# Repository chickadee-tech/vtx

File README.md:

# Chickadee Tech MicroSD Polystack Mod #
This mod adds a VTX to a Polystack.

## Documentation ##
See the [wiki](https://github.com/chickadee-tech/vtx/wiki) for documentation.

## Polystack ##
This **mod** board is part of the Polystack platform for modular microcontrol systems. More information on the platform can be found at [polystack.org](http://polystack.org).

## Support ##
If you need support with a board you own or have development questions please email support@chickadee.tech or check [chickadee.tech/support](https://chickadee.tech/support) for other ways to get support.

## Contributing ##
Please note that this project is released with a [Contributor Code of Conduct](CODE_OF_CONDUCT.md). By participating in this project you agree to abide by its terms.

### Setup ###
Components and footprints for PCB parts are not included in this repository. Instead, checkout the [chickadee-tech/kicad-libs](https://github.com/chickadee-tech/kicad-libs) repository in the same directory that this repository is checked out in. All part definitions should be relative so that they will load correctly.

### Pull requests ###
For fixes please submit a pull request to the original repository. After the pull request is merged, check the [Chickadee Tech Active Contributor Discount (ACD)](https://chickadee.tech/active-contributor) to see if you are eligible for a discount code to use on your next purchase.

### Derivatives ###
If developing your own version of the VTX please remove all Chickadee Tech trademarks and follow the [CC-BY license](LICENSE). While not required, please consider open sourcing your modifications so others can learn from your improvements. If you do email support@chickadee.tech and we may choose to add your project to the ACD.

You may also license the Polystack logo for free by emailing support@chickadee.tech. We'll ask for your gerbers to ensure the design complies with specifications laid out [here](https://github.com/chickadee-tech/polystack/wiki) and provide written permission to use the trademark after compliance has been demonstrated.

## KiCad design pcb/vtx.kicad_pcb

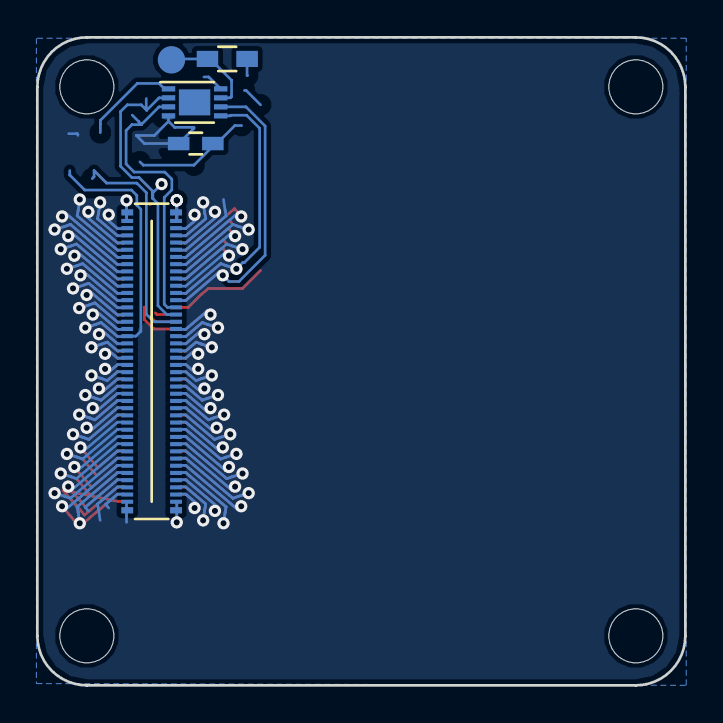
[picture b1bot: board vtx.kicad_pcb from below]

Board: 2 copper layers, 36.0 x 36.0 mm, 5 parts (5 on the bottom side), 3 nets.

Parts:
PORT_C1: 0.1uF; C_0603_HandSoldering
PORT_IC1: AT24CS02-MAHM; DFN-8-1EP_3x2mm_Pitch0.5mm
PORT_IN1: DF40-80pin-Header
PORT_P1: CONN_01X01; Measurement_Point_Round-SMD-Pad_Small
PORT_R1: 10k; R_0603_HandSoldering

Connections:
/ExpansionPort/3V3_0.3A_LL: PORT_C1.1, PORT_IC1.8, PORT_R1.2
GNDPWR: PORT_C1.2, PORT_IC1.4
unnamed: PORT_IC1.7, PORT_R1.1

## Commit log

2016-08-08 Basic files.
2016-08-08 Initial auto-gened PCB files.
